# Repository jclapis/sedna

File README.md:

## Welcome to GitHub Pages

You can use the [editor on GitHub](https://github.com/jclapis/sedna/edit/master/README.md) to maintain and preview the content for your website in Markdown files.

Whenever you commit to this repository, GitHub Pages will run [Jekyll](https://jekyllrb.com/) to rebuild the pages in your site, from the content in your Markdown files.

### Markdown

Markdown is a lightweight and easy-to-use syntax for styling your writing. It includes conventions for

```markdown
Syntax highlighted code block

# Header 1
## Header 2
### Header 3

- Bulleted
- List

1. Numbered
2. List

**Bold** and _Italic_ and `Code` text

[Link](url) and 
```

For more details see [GitHub Flavored Markdown](https://guides.github.com/features/mastering-markdown/).

### Jekyll Themes

Your Pages site will use the layout and styles from the Jekyll theme you have selected in your [repository settings](https://github.com/jclapis/sedna/settings). The name of this theme is saved in the Jekyll `_config.yml` configuration file.

### Support or Contact

Having trouble with Pages? Check out our [documentation](https://help.github.com/categories/github-pages-basics/) or [contact support](https://github.com/contact) and we’ll help you sort it out.

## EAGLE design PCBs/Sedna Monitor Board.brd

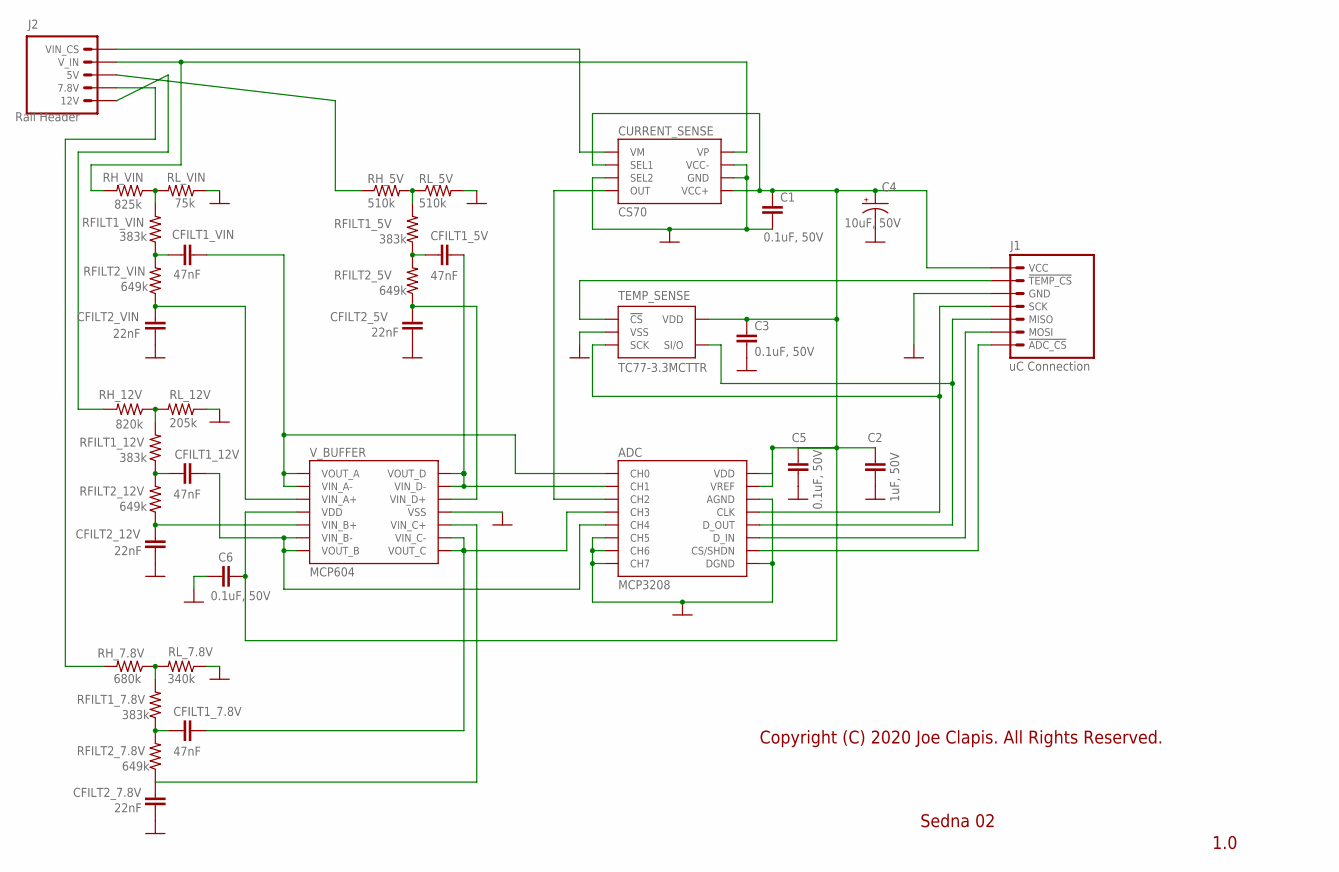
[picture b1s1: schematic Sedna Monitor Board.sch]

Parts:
ADC: MCP3208; MICROCHIP_SOIC-16_SL
C1, C3, C5, C6: 0.1uF, 50V; C0805
C2: 1uF, 50V; C0805
C4: 10uF, 50V; PANASONIC-SMD-CAP-SV-D
CFILT1_5V, CFILT1_7.8V, CFILT1_12V, CFILT1_VIN: 47nF; C0805
CFILT2_5V, CFILT2_7.8V, CFILT2_12V, CFILT2_VIN: 22nF; C0805
CURRENT_SENSE: CS70; TSSOP8
J1: uC Connection; 1X07
J2: Rail Header; 1X05
RFILT1_5V, RFILT1_7.8V, RFILT1_12V, RFILT1_VIN: 383k; R0805
RFILT2_5V, RFILT2_7.8V, RFILT2_12V, RFILT2_VIN: 649k; R0805
RH_5V: 510k; R0805
RH_7.8V: 680k; R0805
RH_12V: 820k; R0805
RH_VIN: 825k; R0805
RL_5V: 510k; R0805
RL_7.8V: 340k; R0805
RL_12V: 205k; R0805
RL_VIN: 75k; R0805
TEMP_SENSE: TC77-3.3MCTTR; MICROCHIP_SOT-23_5_OT
V_BUFFER: MCP604; MICROCHIP_TSSOP-14_ST

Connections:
ADC_CS: ADC.10 (CS/SHDN), J1.7 (!ADC_CS)
CS_OUT: ADC.3 (CH2), CURRENT_SENSE.4 (OUT)
GND: ADC.6 (CH5), ADC.7 (CH6), ADC.8 (CH7), ADC.9 (DGND), ADC.14 (AGND), C1.2, C2.2, C3.2, C4.GND (-), C5.2, C6.2, CFILT2_5V.1, CFILT2_7.8V.1, CFILT2_12V.1, CFILT2_VIN.1, CURRENT_SENSE.3 (SEL2), CURRENT_SENSE.6 (GND), CURRENT_SENSE.7 (VCC-), J1.3 (GND), RL_5V.2, RL_7.8V.1, RL_12V.1, RL_VIN.1, TEMP_SENSE.2 (VSS), V_BUFFER.11 (VSS)
MOSI: ADC.11 (D_IN), J1.6 (MOSI)
unnamed: ADC.12 (D_OUT), J1.5 (MISO), TEMP_SENSE.4 (SI/O)
unnamed: CURRENT_SENSE.1 (VM), J2.1 (VIN_CS)
unnamed: CURRENT_SENSE.8 (VP), J2.2 (V_IN), RH_VIN.2
unnamed: J2.4 (7.8V), RH_7.8V.2
unnamed: J2.3 (5V), RH_5V.1
unnamed: RFILT1_12V.2, RH_12V.1, RL_12V.2
unnamed: CFILT2_VIN.2, RFILT2_VIN.1, V_BUFFER.3 (VIN_A+)
unnamed: CFILT1_VIN.1, RFILT1_VIN.1, RFILT2_VIN.2
unnamed: J2.5 (12V), RH_12V.2
unnamed: RFILT1_VIN.2, RH_VIN.1, RL_VIN.2
unnamed: CFILT2_12V.2, RFILT2_12V.1, V_BUFFER.5 (VIN_B+)
unnamed: CFILT1_7.8V.2, RFILT1_7.8V.1, RFILT2_7.8V.2
unnamed: CFILT2_7.8V.2, RFILT2_7.8V.1, V_BUFFER.10 (VIN_C+)
unnamed: RFILT1_7.8V.2, RH_7.8V.1, RL_7.8V.2
unnamed: CFILT1_12V.1, RFILT1_12V.1, RFILT2_12V.2
unnamed: RFILT1_5V.2, RH_5V.2, RL_5V.1
unnamed: CFILT1_5V.2, RFILT1_5V.1, RFILT2_5V.2
unnamed: CFILT2_5V.2, RFILT2_5V.1, V_BUFFER.12 (VIN_D+)
SCK: ADC.13 (CLK), J1.4 (SCK), TEMP_SENSE.3 (SCK)
TC77_CS: J1.2 (!TEMP_CS), TEMP_SENSE.1 (!CS)
VDD: ADC.15 (VREF), ADC.16 (VDD), C1.1, C2.1, C3.1, C4.VDD (+), C5.1, C6.1, CURRENT_SENSE.2 (SEL1), CURRENT_SENSE.5 (VCC+), J1.1 (VCC), TEMP_SENSE.5 (VDD), V_BUFFER.4 (VDD)
VOUT_A: ADC.1 (CH0), CFILT1_VIN.2, V_BUFFER.1 (VOUT_A), V_BUFFER.2 (VIN_A-)
VOUT_B: ADC.5 (CH4), CFILT1_12V.2, V_BUFFER.6 (VIN_B-), V_BUFFER.7 (VOUT_B)
VOUT_C: ADC.4 (CH3), CFILT1_7.8V.1, V_BUFFER.8 (VOUT_C), V_BUFFER.9 (VIN_C-)
VOUT_D: ADC.2 (CH1), CFILT1_5V.1, V_BUFFER.13 (VIN_D-), V_BUFFER.14 (VOUT_D)

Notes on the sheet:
Sedna 02
1.0
Copyright (C) 2020 Joe Clapis. All Rights Reserved.

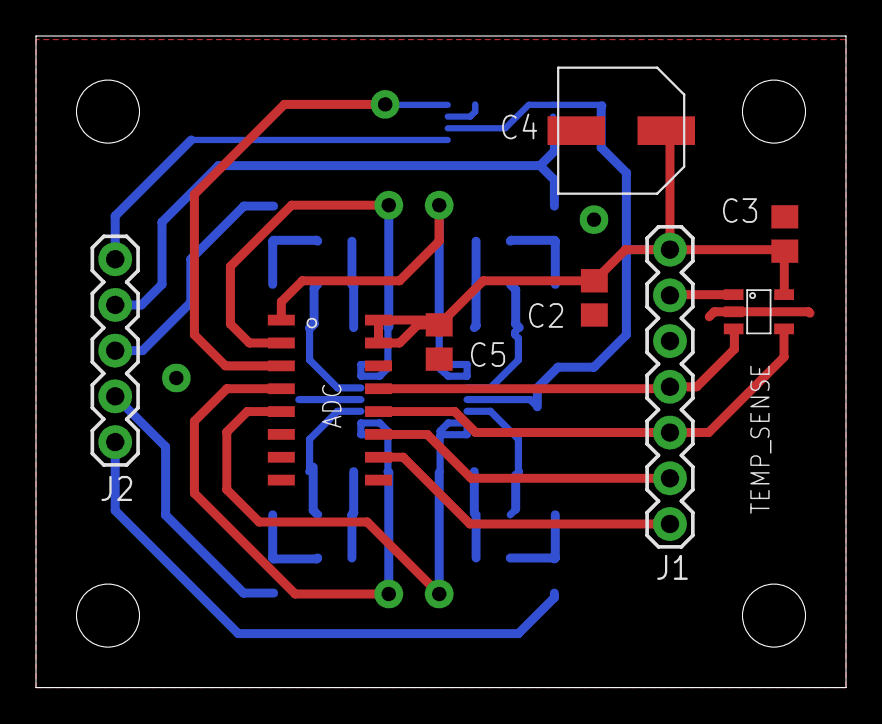
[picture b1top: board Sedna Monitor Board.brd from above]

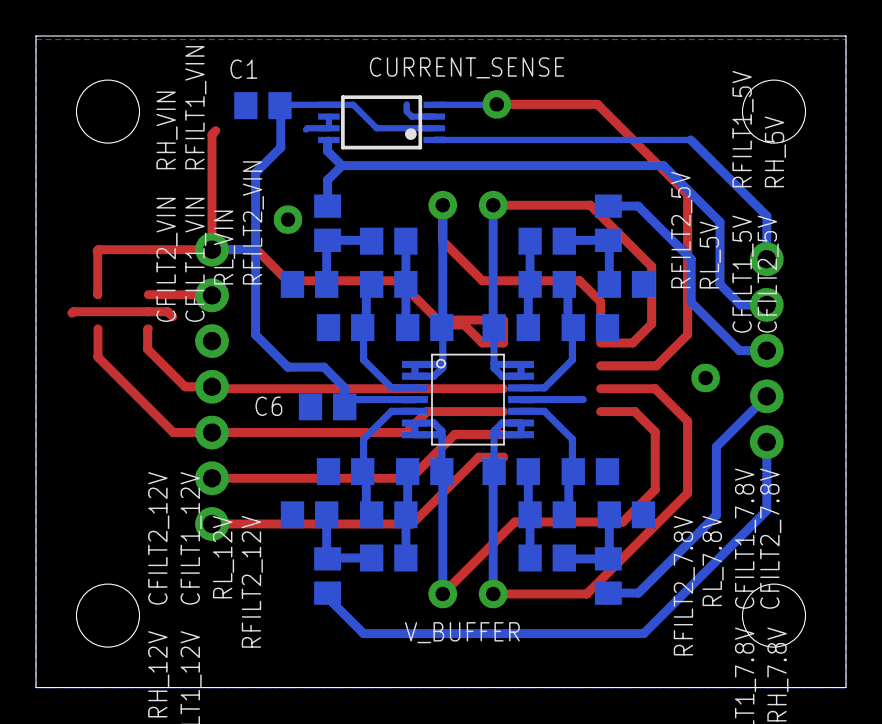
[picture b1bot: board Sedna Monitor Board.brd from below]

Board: 2 copper layers, 45.0 x 36.2 mm, 36 parts (28 on the bottom side), 29 nets.

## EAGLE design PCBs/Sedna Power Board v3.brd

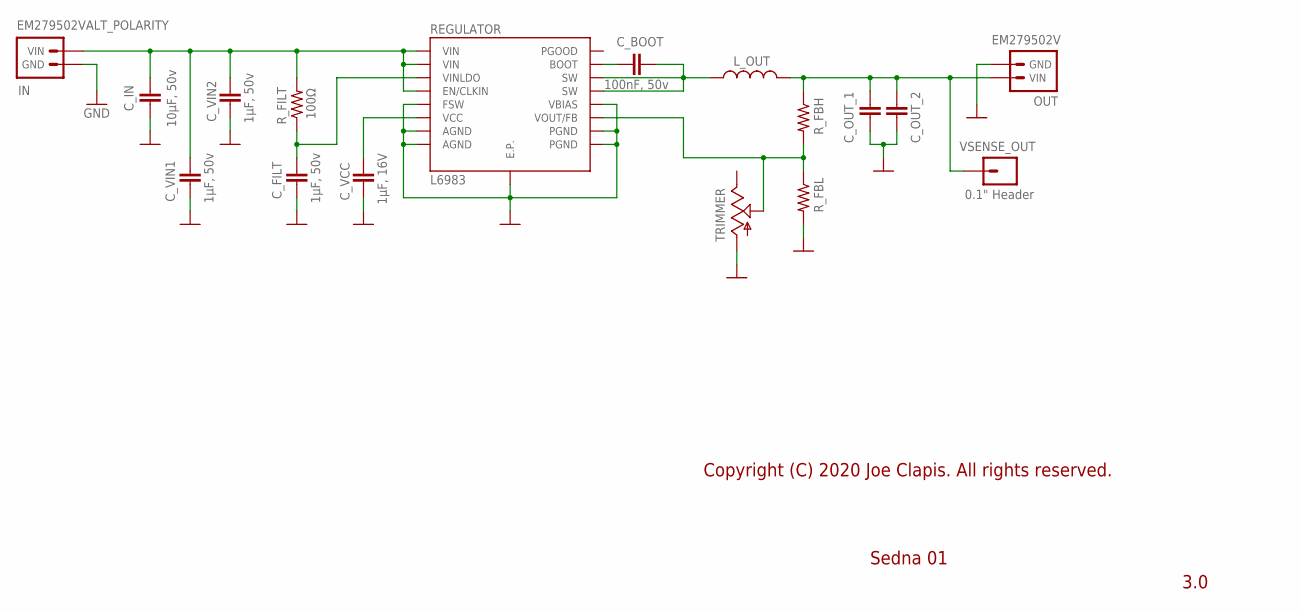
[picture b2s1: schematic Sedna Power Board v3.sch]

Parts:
C_BOOT: 100nF, 50v; C0805
C_FILT: 1μF, 50v; C0805
C_IN: 10μF, 50v; C1206
C_OUT_1, C_OUT_2: TDK_C2220_5750
C_VCC: 1μF, 16V; C0805
C_VIN1, C_VIN2: 1μF, 50v; C0805
IN: EM279502VALT_POLARITY; EM279502V
L_OUT: PA4343_FP2
OUT: EM279502V
REGULATOR: L6983
R_FBH: R-US_R0805; R0805
R_FBL: R-US_R0805; R0805
R_FILT: 100Ω; R0805
TRIMMER: BOURNS_3361S
VSENSE_OUT: 0.1" Header; 1X01

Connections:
C_BOOT: C_BOOT.1, REGULATOR.11_BOOT (BOOT)
FB: REGULATOR.7_FB/VOUT (VOUT/FB), R_FBH.2, R_FBL.1, TRIMMER.2 (S)
GND: C_FILT.2, C_IN.2, C_OUT_1.2, C_OUT_2.2, C_VCC.2, C_VIN1.2, C_VIN2.2, IN.1A (GND), IN.1B (GND), OUT.2A (GND), OUT.2B (GND), REGULATOR.3_AGND (AGND), REGULATOR.6_VBIAS (VBIAS), REGULATOR.8_FSW (FSW), REGULATOR.10_AGND (AGND), REGULATOR.13_PGND (PGND), REGULATOR.16_PGND (PGND), REGULATOR.E.P., R_FBL.2, TRIMMER.1 (A)
SW_OUT: C_BOOT.2, L_OUT.1, REGULATOR.14_SW (SW), REGULATOR.15_SW (SW)
VCC: C_VCC.1, REGULATOR.9_VCC (VCC)
VINLDO: C_FILT.1, REGULATOR.2_VINLDO (VINLDO), R_FILT.1
V_IN: C_IN.1, C_VIN1.1, C_VIN2.1, IN.2A (VIN), IN.2B (VIN), REGULATOR.1_VIN (VIN), REGULATOR.4_EN/CLKIN (EN/CLKIN), REGULATOR.12_VIN (VIN), R_FILT.2
V_OUT: C_OUT_1.1, C_OUT_2.1, L_OUT.2, OUT.1A (VIN), OUT.1B (VIN), R_FBH.1, VSENSE_OUT.1

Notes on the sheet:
Sedna 01
3.0
Copyright (C) 2020 Joe Clapis. All rights reserved.

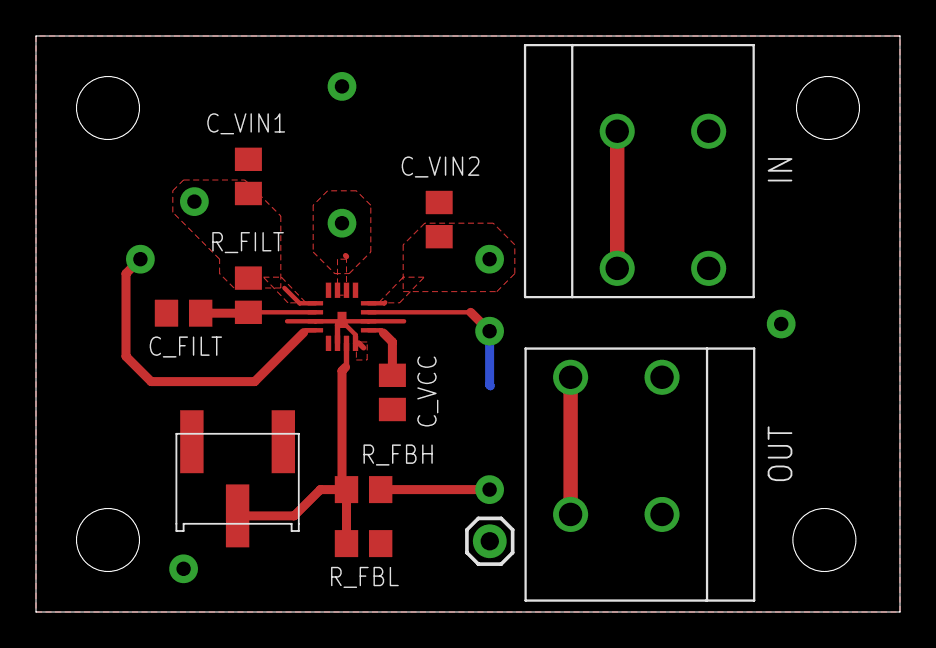
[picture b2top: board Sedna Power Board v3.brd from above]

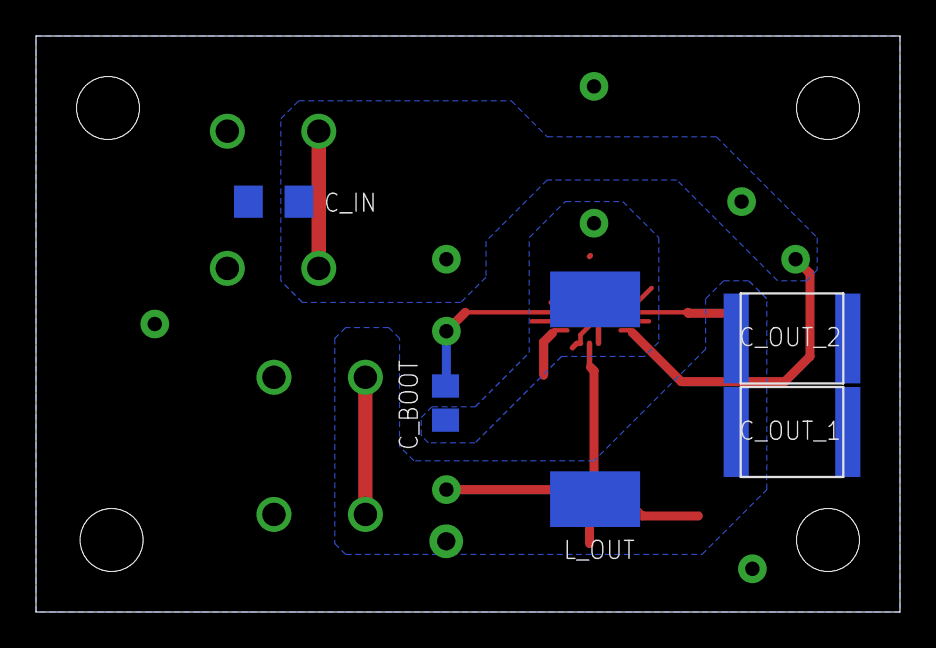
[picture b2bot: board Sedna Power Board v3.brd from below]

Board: 2 copper layers, 48.0 x 32.0 mm, 17 parts (5 on the bottom side), 8 nets.

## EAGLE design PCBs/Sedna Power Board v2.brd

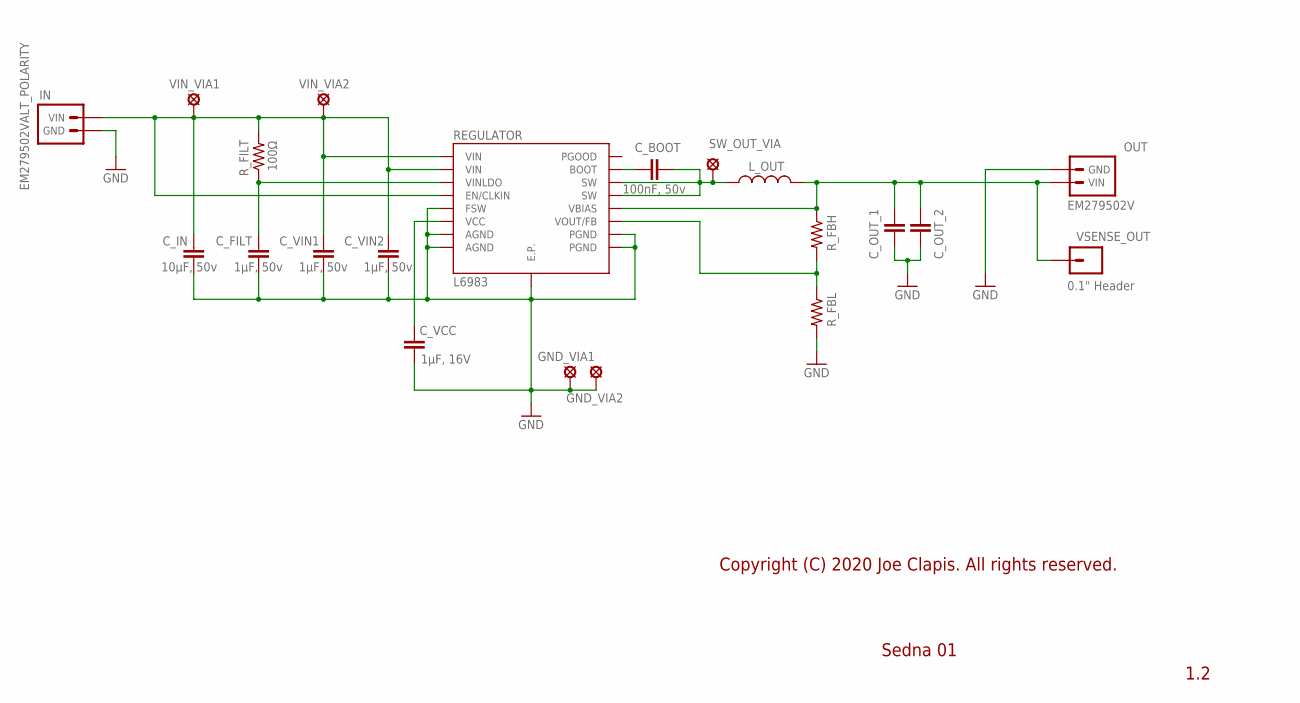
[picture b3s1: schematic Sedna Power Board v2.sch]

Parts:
C_BOOT: 100nF, 50v; C0805
C_FILT: 1μF, 50v; C0805
C_IN: 10μF, 50v; C1206
C_OUT_1, C_OUT_2: TDK_C2220_5750
C_VCC: 1μF, 16V; C0805
C_VIN1, C_VIN2: 1μF, 50v; C0805
GND_VIA1, GND_VIA2: LSP13
IN: EM279502VALT_POLARITY; EM279502V
L_OUT: PA4343_FP2
OUT: EM279502V
REGULATOR: L6983
R_FBH: R-US_R0805; R0805
R_FBL: R-US_R0805; R0805
R_FILT: 100Ω; R0805
SW_OUT_VIA: LSP13
VIN_VIA1, VIN_VIA2: LSP13
VSENSE_OUT: 0.1" Header; 1X01

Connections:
C_BOOT: C_BOOT.1, REGULATOR.11_BOOT (BOOT)
FB: REGULATOR.7_FB/VOUT (VOUT/FB), R_FBH.2, R_FBL.1
GND: C_FILT.2, C_IN.2, C_OUT_1.2, C_OUT_2.2, C_VCC.2, C_VIN1.2, C_VIN2.2, GND_VIA1.MP, GND_VIA2.MP, IN.1A (GND), IN.1B (GND), OUT.2A (GND), OUT.2B (GND), REGULATOR.3_AGND (AGND), REGULATOR.8_FSW (FSW), REGULATOR.10_AGND (AGND), REGULATOR.13_PGND (PGND), REGULATOR.16_PGND (PGND), REGULATOR.E.P., R_FBL.2
SW_OUT: C_BOOT.2, L_OUT.1, REGULATOR.14_SW (SW), REGULATOR.15_SW (SW), SW_OUT_VIA.MP
VCC: C_VCC.1, REGULATOR.9_VCC (VCC)
VINLDO: C_FILT.1, REGULATOR.2_VINLDO (VINLDO), R_FILT.1
V_IN: C_IN.1, C_VIN1.1, C_VIN2.1, IN.2A (VIN), IN.2B (VIN), REGULATOR.1_VIN (VIN), REGULATOR.4_EN/CLKIN (EN/CLKIN), REGULATOR.12_VIN (VIN), R_FILT.2, VIN_VIA1.MP, VIN_VIA2.MP
V_OUT: C_OUT_1.1, C_OUT_2.1, L_OUT.2, OUT.1A (VIN), OUT.1B (VIN), REGULATOR.6_VBIAS (VBIAS), R_FBH.1, VSENSE_OUT.1

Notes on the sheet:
Sedna 01
1.2
Copyright (C) 2020 Joe Clapis. All rights reserved.

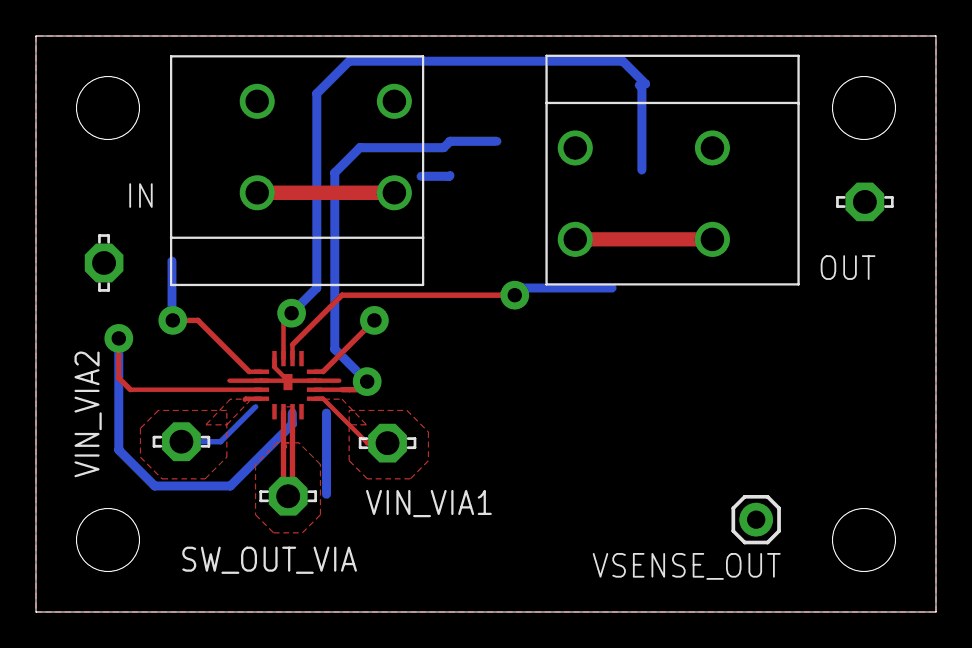
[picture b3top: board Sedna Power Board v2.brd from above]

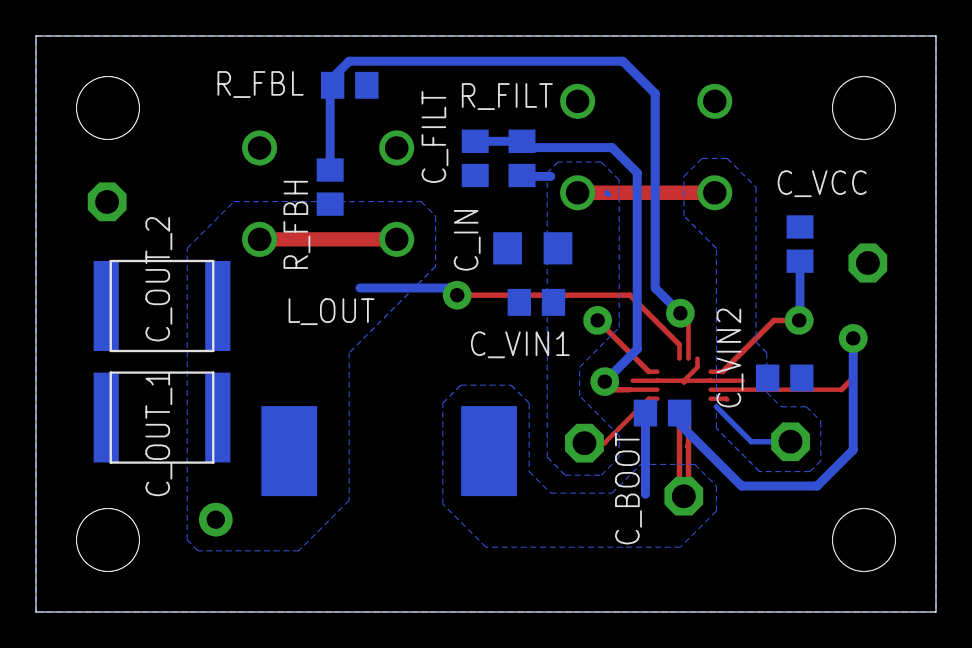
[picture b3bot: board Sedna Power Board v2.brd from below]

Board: 2 copper layers, 50.0 x 32.0 mm, 21 parts (12 on the bottom side), 8 nets.

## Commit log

2020-02-09 Initial push - proof of concept UI is working! It can detect cameras and get/set the ISO setting.
2020-02-09 Temporarily including the C# gphoto2 binding as a nupkg here until I can officially publish it.
2020-02-09 Refactored the camera stuff into a new CameraManager class, wrapped the exposure box into a spinner that supports selection-based displays
2020-02-10 Added a simple image capture feature
2020-02-10 Added file saving support and a few image tab improvements
2020-02-11 Added support for changing the live view mode, started working on the viewfinder but it's going to be hard to do efficiently.
2020-02-12 Set theme jekyll-theme-slate
2020-02-12 Added preview functionality, though I'm still going to play with it to make it go faster. It's kind of capped at 15ish FPS on the Pi.
2020-02-13 Live view now uses libjpeg-turbo and some WriteableBitmap shenanigans, which is about 50x faster than the old way. I'm very happy with it now!
2020-02-13 Added the ARM64 libraries for SkiaSharp and libjpeg-turbo. It's probably best to keep them in the repo in case something happens to the Pi.
2020-02-16 Added crosshairs to the viewfinder, started working on the motor control layout
2020-02-19 Started modularizing the camera settings instead of hardcoding them, but this can wait until the whole thing is functional.
2020-02-19 Started working on the low-level motor control (SPI) code.
2020-02-19 Started importing the L6470 AutoDriver library from SparkFun.
2020-02-20 Refactored a bit, so most of the logic will be C++ with a simple C wrapper that C# can interface with. The AutoDriver library is all C++ so I'd have to do this anyway in order to work with it.
2020-02-20 Created a class for the AMT22 rotary encoders
2020-02-22 More L6470 progress. I decided to just include the stuff that I plan to use, instead of writing a complete binding for the entire chip.
2020-02-23 Switched to using well-sized types (like uint8_t), just better practice. Lots of work on L6470.
2020-02-23 Finished the initialization stuff for the L6470. Now to do the relevant settings and functions!
2020-02-23 Decided to move all of the high-level AMT22 / L6470 code over to the C# project because it's just easier to maintain. The SPI stuff will still be in C though; I made a new library called PiSpi for th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
2020-02-23 Finished moving the motor control code over to C#
2020-02-23 PiSpi was misconfigured and using old SednaMotorControl files, fixed that so they're included now
2020-02-23 Made a simple debug UI to start testing things, but I don't have the cabling so this will have to wait for a bit until I can hook everything up.
2020-03-06 Been a while! I've been working in CAD land on the hardware side of the focusing assembly, and now I'm happy to commit it here too.
2020-03-08 Fixed a few small bugs in PiSpi
2020-03-08 Fixed a bug with SPI comms, added access to the motor control window
2020-03-08 Fixed a major timing problem with the way the Pi's SPI clock works when you flip back and forth between devices that use different clock polarities. This one took a while to hunt down.
2020-03-08 Added logging support to AMT22
2020-03-08 Started making a focus assembly class for managing the entire focuser
2020-03-09 Finished a first pass of the focus assembly... time to see if it works!
2020-03-09 Added support to PiSpi for ignoring delays when the device is faster than the SPI clock cycle, because even delayMicrosecond(0) causes a signicant delay
2020-03-09 Messing with the L6470, it isn't behaving right so it needs some debugging.
2020-03-12 Fixed the L6470 code so SPI comms work now! (It requires CS to be set to high and then back to low after every byte instead of every transaction...)
    Also added some extra bugfixes to the MotorControlWindow.
2020-03-12 Got the focus control on the main page (mostly) working! It oscillates a lot at the end so i need to include some kind of PID acceleration ramp, but it works!!
2020-03-12 Added a rudimentary acceleration curve setup, the focuser officially works perfectly now! This is a MAJOR milestone!
2020-03-17 Started working on the schematic for the power circuit
2020-03-20 Finished the 12v and 7.2v circuits, started working on the current sensing setup
2020-03-26 I decided the giant monolithic PCB isn't the way to start, so I started making individual breakout-style boards for all of the SMDs. Meet v1.0 of the L6983 power board!
2020-05-10 Now that the laser engraver is done, I can start fabricating some boards. Updated the power board to v1.1, put together a BOM to make 3 of them at 12v, 7.2v, and 5v.
2020-05-13 Redid the power board layout, trying a thinner but longer variant which should help cable management.
2020-05-19 Started working on v2 of the power board - double sided, smaller, should be much easier to etch and populate for a homebrew setup.
2020-05-30 v2.0.2 of the power board - still prototyping, still learning...
2020-05-30 v3 of the power board, now with a trimpot on the FB voltage divider for output voltage adjustments.
2020-06-01 Finished the schematic for the monitor board
2020-06-06 Started working on the Monitor Board layout
2020-06-07 Finished the Monitor Board v1.0

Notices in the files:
parts and their libraries:
SparkFun-Connectors: Licensing: Creative Commons ShareAlike 4.0 International - https://creativecommons.org/licenses/by-sa/4.0
